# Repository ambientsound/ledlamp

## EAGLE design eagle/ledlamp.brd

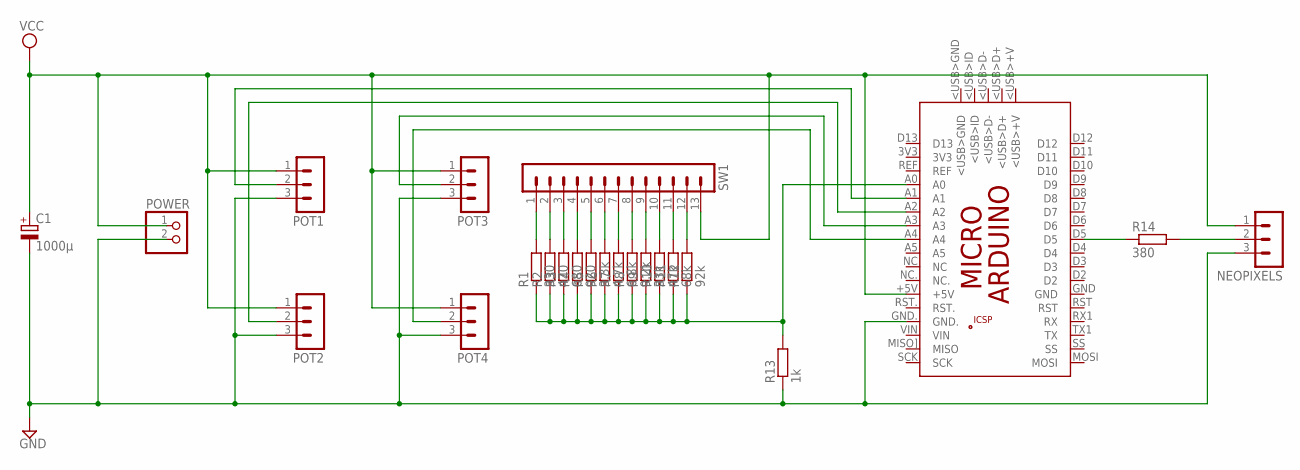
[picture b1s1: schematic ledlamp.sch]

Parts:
C1: 1000µ; E5-8,5
NEOPIXELS: MA03-1
PCB1: ARDUINO_MICRO
POT1, POT2, POT3, POT4: MA03-1
POWER: PINHD-1X2; 1X02
R1: 330; 0207/10
R2: 470; 0207/10
R3: 680; 0207/10
R4: 920; 0207/10
R5: 3.3k; 0207/10
R6: 4.7k; 0207/10
R7: 6.8k; 0207/10
R8: 9.2k; 0207/10
R9: 33k; 0207/10
R10: 47k; 0207/10
R11: 68k; 0207/10
R12: 92k; 0207/10
R13: 1k; 0207/10
R14: 380; 0207/10
SW1: MA13-1

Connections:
GND: C1.-, NEOPIXELS.3, PCB1.GND., POT1.3, POT2.3, POT3.3, POT4.3, POWER.2, R13.1
unnamed: R1.2, SW1.1
unnamed: R2.2, SW1.2
unnamed: R3.2, SW1.3
unnamed: R4.2, SW1.4
unnamed: R5.2, SW1.5
unnamed: R6.2, SW1.6
unnamed: R7.2, SW1.7
unnamed: R8.2, SW1.8
unnamed: R9.2, SW1.9
unnamed: R10.2, SW1.10
unnamed: R11.2, SW1.11
unnamed: R12.2, SW1.12
unnamed: PCB1.A0, R1.1, R2.1, R3.1, R4.1, R5.1, R6.1, R7.1, R8.1, R9.1, R10.1, R11.1, R12.1, R13.2
unnamed: PCB1.A1, POT1.2
unnamed: PCB1.A2, POT2.2
unnamed: PCB1.A3, POT3.2
unnamed: PCB1.A4, POT4.2
unnamed: PCB1.D5, R14.1
unnamed: NEOPIXELS.2, R14.2
VCC: C1.+, NEOPIXELS.1, PCB1.+5V, POT1.1, POT2.1, POT3.1, POT4.1, POWER.1, SW1.13

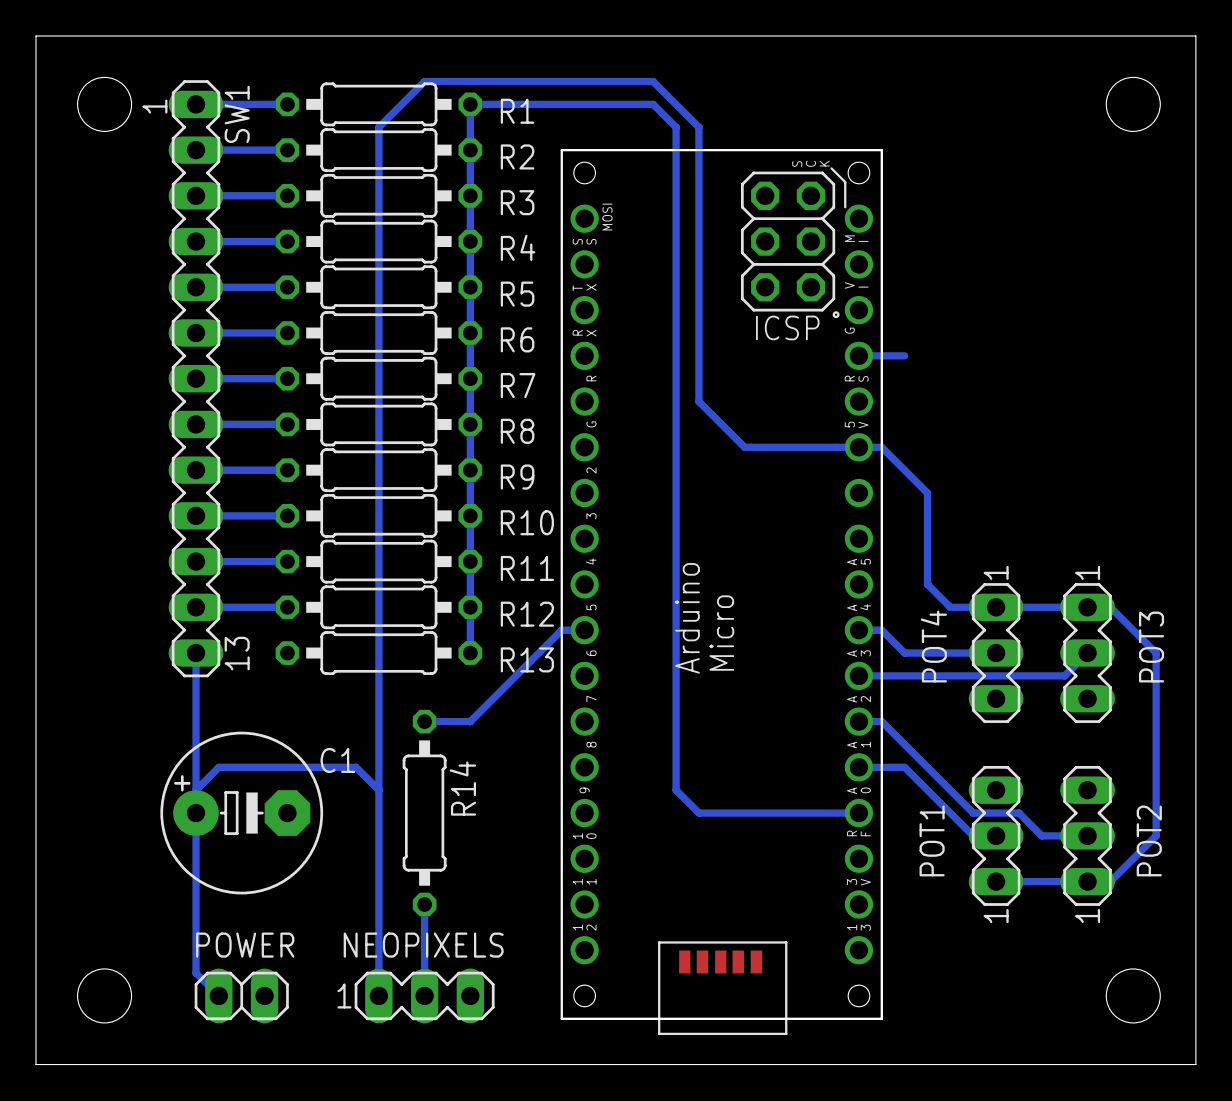
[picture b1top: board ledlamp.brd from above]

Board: 2 copper layers, 64.3 x 57.0 mm, 23 parts (0 on the bottom side), 21 nets.

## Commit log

2015-09-27 Add CAD files for the hardware container
2015-09-27 Add EAGLE schematics of imagined PCB
2015-09-28 Add drill holes from PCB to panel drawing
2015-09-28 Add pull-down resistor as voltage divider for A0
2015-10-02 Add Arduino code
